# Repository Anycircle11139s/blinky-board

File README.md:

# blinky-board
This is my stasis blinky board, I created it based on the starter project and I made it my own by creating it in a creeper and adding eyes.
Screenshot of 3d view:

<br>
Making it IRL:
I spent about 3 hours soldering everything together and I when I ran power through the blinky board, it actually worked. I'm really grateful that it worked out and I'm really proud of myself for being able to create something like that.
<br>

<br>

https://github.com/user-attachments/assets/a71cb91d-c118-4e68-b43b-3124663b7815

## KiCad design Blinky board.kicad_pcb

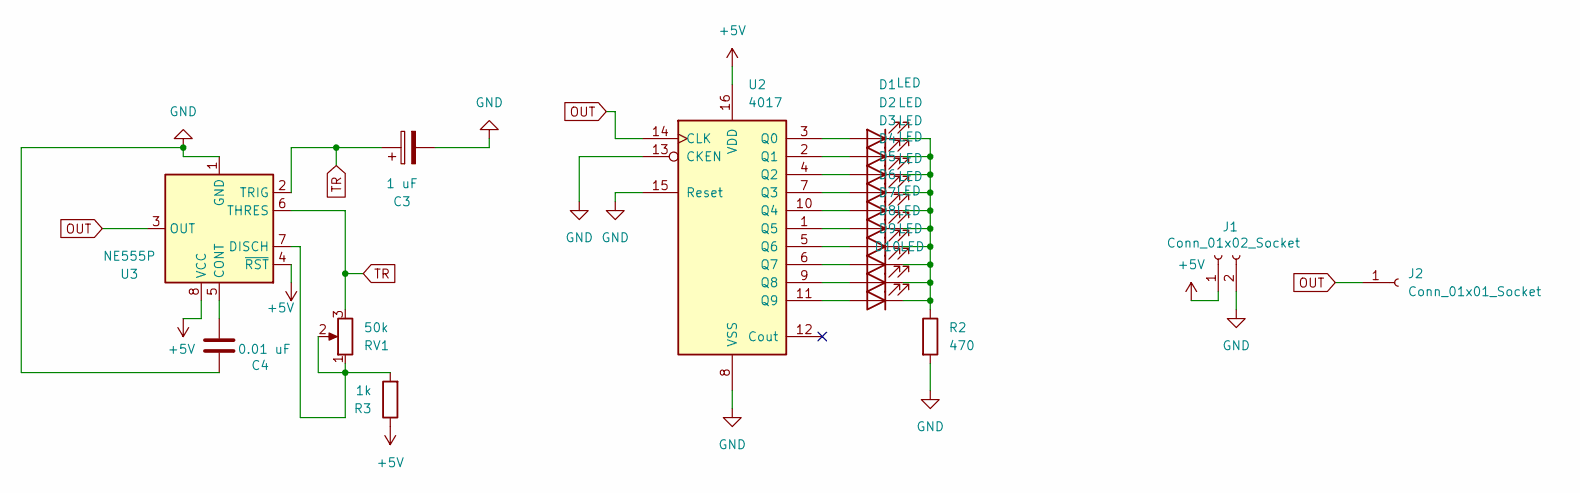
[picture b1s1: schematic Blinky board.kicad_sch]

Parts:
C3: 1 uF; CP_Radial_D5.0mm_P2.00mm
C4: 0.01 uF; C_Disc_D7.5mm_W2.5mm_P5.00mm
D1, D2, D3, D4, D5, D6, D7, D8, D9, D10: LED; LED_D3.0mm
J1: Conn_01x02_Socket; PinHeader_1x02_P2.54mm_Vertical
J2: Conn_01x01_Socket; PinHeader_1x01_P2.54mm_Vertical
R2: 470; R_Axial_DIN0207_L6.3mm_D2.5mm_P7.62mm_Horizontal
R3: 1k; R_Axial_DIN0207_L6.3mm_D2.5mm_P7.62mm_Horizontal
RV1: 50k; Potentiometer_Vishay_T93YA_Vertical
U2: 4017; N16
U3: NE555P; DIP-8_W7.62mm

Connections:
+5V: J1.1, R3.1, U2.16 (VDD), U3.4 (~RST), U3.8 (VCC)
GND: C3.2, C4.2, J1.2, R2.2, U2.8 (VSS), U2.13 (CKEN), U2.15 (Reset), U3.1 (GND)
unnamed: D1.2 (A), U2.3 (Q0)
unnamed: D1.1 (K), D2.1 (K), D3.1 (K), D4.1 (K), D5.1 (K), D6.1 (K), D7.1 (K), D8.1 (K), D9.1 (K), D10.1 (K), R2.1
unnamed: D2.2 (A), U2.2 (Q1)
unnamed: D3.2 (A), U2.4 (Q2)
unnamed: D4.2 (A), U2.7 (Q3)
unnamed: D5.2 (A), U2.10 (Q4)
unnamed: D6.2 (A), U2.1 (Q5)
unnamed: D7.2 (A), U2.5 (Q6)
unnamed: D8.2 (A), U2.6 (Q7)
unnamed: D9.2 (A), U2.9 (Q8)
unnamed: D10.2 (A), U2.11 (Q9)
unnamed: C4.1, U3.5 (CONT)
unnamed: R3.2, RV1.1, RV1.2, U3.7 (DISCH)
OUT: J2.1, U2.14 (CLK), U3.3 (OUT)
TR: C3.1, RV1.3, U3.2 (TRIG), U3.6 (THRES)

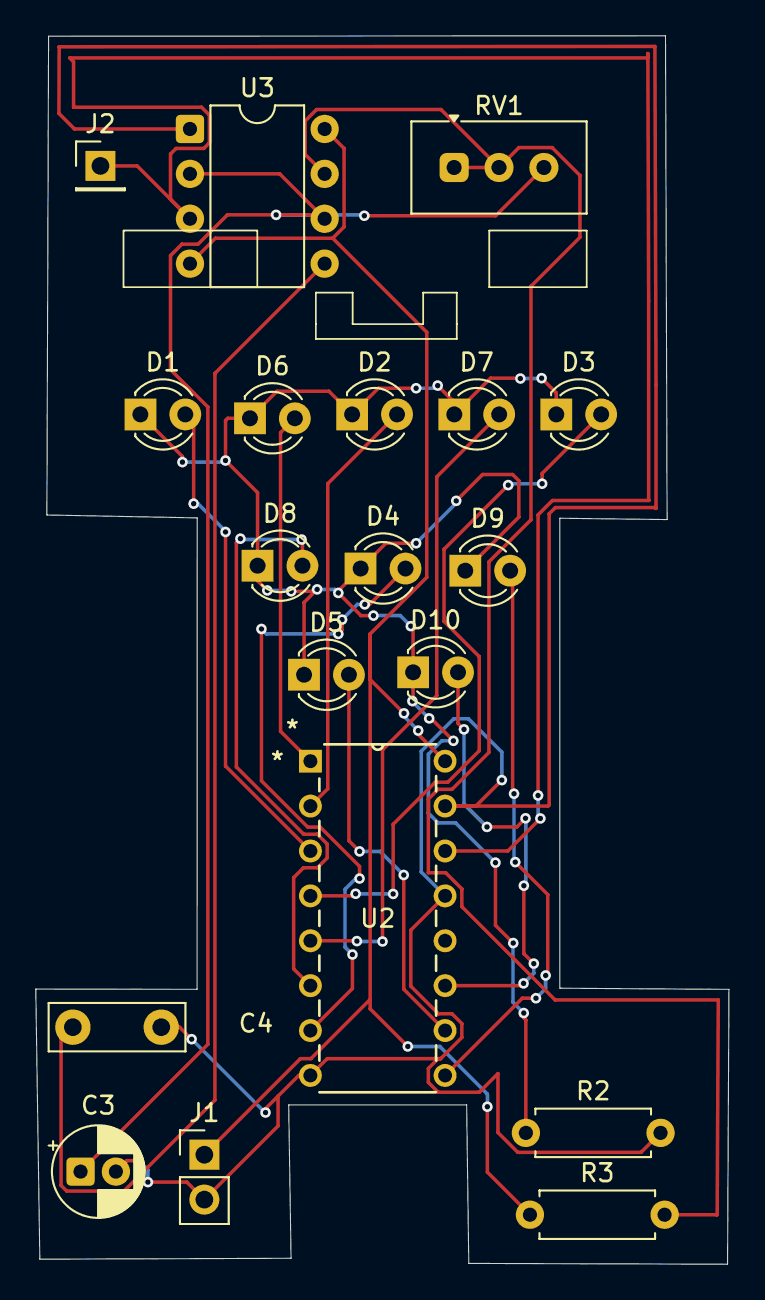
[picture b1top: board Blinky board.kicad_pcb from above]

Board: 2 copper layers, 39.2 x 69.5 mm, 19 parts (0 on the bottom side), 17 nets.
